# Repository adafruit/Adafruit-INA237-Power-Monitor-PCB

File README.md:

## Adafruit INA237 85V 10A 16-bit DC Current Voltage Power Monitor - STEMMA QT PCB

<a href="http://www.adafruit.com/products/6340"><br/>
Click here to purchase one from the Adafruit shop</a>

PCB files for the Adafruit INA237 85V 10A 16-bit DC Current Voltage Power Monitor - STEMMA QT. 

Format is EagleCAD schematic and board layout
* https://www.adafruit.com/product/6340

### Description

The INA237 is an amazing power monitoring chip, with best-of-everything support: up to 85VDC common-mode, high or low side measurements, 16-bit ADC for precision measurements from milliamp to Amp, and I2C interface for easy configuration of alerts, oversampling, gain adjustments and more!

The INA237 is similar to the INA228, with the same:

* up to +85V high or low-side measurements
* up to 10A or 2.75A
* current, voltage and power measurements

However, unlike the INA228 the INA237:

* has only 16-bit resolution, so 0.15mA or 42uA LSB rather than 10uA/2.5uA
* the INA228 can measure energy/charge for you but the INA237 cannot
* 0.3% gain error, ±50 µV max offset voltage compared to INA228's 0.05% gain error, ±1 µV

This breakout board may well be the last current sensing solution you every need to buy. Not only can it do the work of two multimeters, but it can do it with amazing precision and flexibility. With it you can measure high or low side DC current, the bus voltage, and have it automatically calculate the power. It can do so over impressive voltage, current, and temperature ranges with better than 1% accuracy, all while delivering the data in an easy to use format over I2C.

Works great with any microcontroller that is CircuitPython or Arduino compatible as well as single board computers such as the Raspberry Pi. It is compatible with 3V or 5V logic and can measure bus voltages up to +85VDC. Not for use with AC voltages.

Most current-measuring devices operate with some notable constraints that limit what they can be used for. Many are low-side only which can cause issues as the ground reference changes with current. Others like its little sister the INA219B avoid this by measuring on the high side but need to change their shunt resistor to measure different current ranges. The INA237 avoids these limitations, and with the precision 15milliohm shunt resistor on board, it can be used to measure as much as +85V at up to 10A (~0.15mA per LSB) or 2.75A (~42uA per LSB) Continuous on either the high or low side. Wow!

The voltage across the integrated 15 milliohm (.015 ohms!), 0.1% shunt resistor is measured by the internal 16 bit ADC, allowing for measurements over the current range with a resolution of 0.15mA per LSB in high current measurement mode or 42uA per LSB in low current measurement mode.To measure low-side, Connect VIN- to ground and VIN+ to your load's lowest potential. Cut the jumper on the back that connects VBUS to VIN+: VBUS should connect to the highest project voltage, up to 85V. To measure high-side, connect VIN+ to the highest project voltage, and VIN- to the load's highest potential. In high-side measurement, which is most common, we simplify wiring by having a pre-connected jumper from V+ to VBUS.

Usage is simple. Power the sensor itself with 3 to 5VDC and connect the two I2C pins to your microcontroller. Then connect your target power supply to VIN+ and the load to ground to VIN-. We have a detailed tutorial that will do all the gain, range, and math for you - just plug and go with our Arduino library or CircuitPython! You can connect up to 4 sensors on one bus by soldering the address jumpers on the back.

As if that weren't enough, we also added SparkFun qwiic-compatible STEMMA QT connectors for the I2C bus, so you don't even need to solder the I2C and power lines. Simply wire up to your favorite micro using a STEMMA QT adapter cable. The Stemma QT connectors also mean the INA237 can be used with our various associated accessories. QT Cable is not included, but we have a variety in the shop.

Comes as a fully assembled breakout board with a 3.5mm terminal block and header. Some light soldering is required to attach the header for use in a breadboard. 

### License

Adafruit invests time and resources providing this open source design, please support Adafruit and open-source hardware by purchasing products from [Adafruit](https://www.adafruit.com)!

Designed by Limor Fried/Ladyada for Adafruit Industries.

Creative Commons Attribution/Share-Alike, all text above must be included in any redistribution. 
See license.txt for additional details.

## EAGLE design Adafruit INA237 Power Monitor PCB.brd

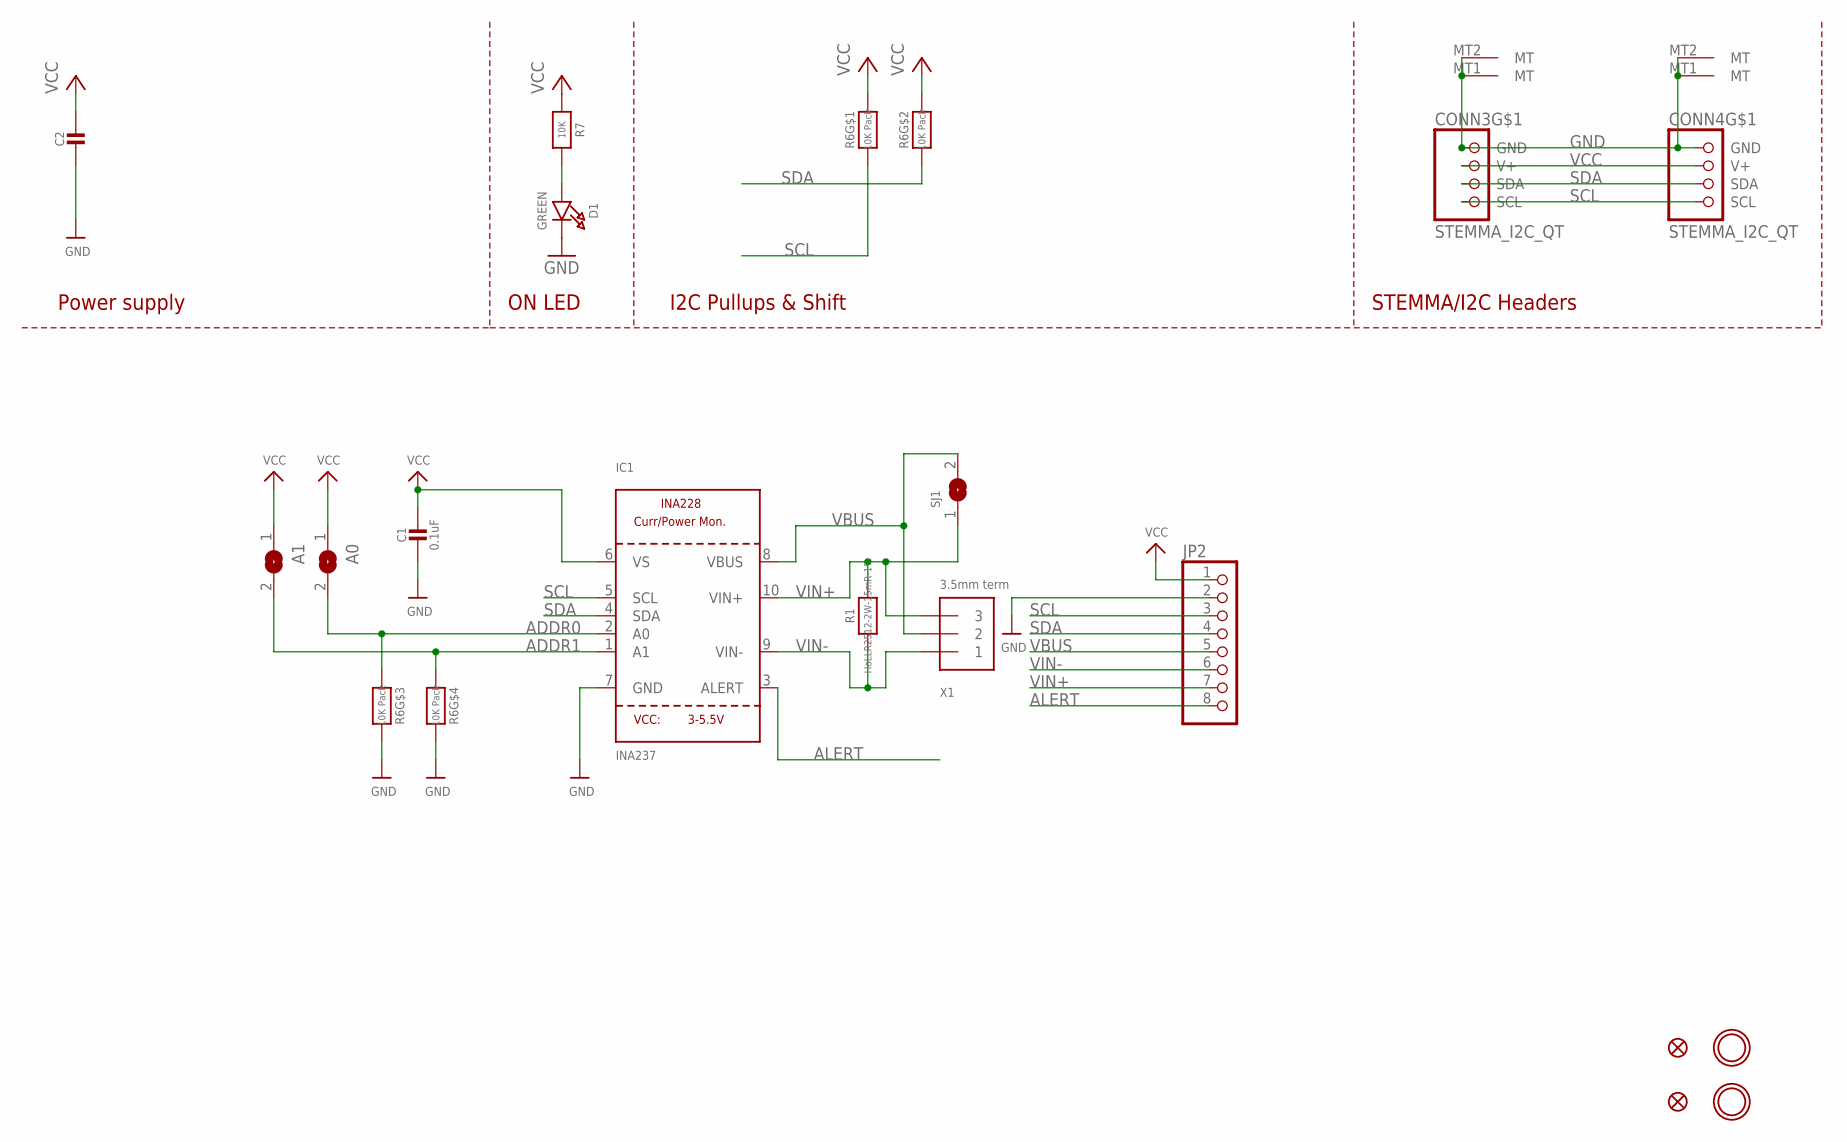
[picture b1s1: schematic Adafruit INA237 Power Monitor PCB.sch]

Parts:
A0, A1: SOLDERJUMPERREFLOW_NOPASTE; SOLDERJUMPER_REFLOW_NOPASTE
C1: 0.1uF; 0603-NO
C2: 10uF; 0805-NO
CONN3, CONN4: STEMMA_I2C_QT; JST_SH4
D1: GREEN; CHIPLED_0603_NOOUTLINE
FID3, FID4: FIDUCIAL_1MM
IC1: INA237; MSOP10
JP2: HEADER-1X870MIL; 1X08_ROUND_70
R1: HoLLR2512-2W-15mR-1%; 2512
R6: 10K Pack; RESPACK_4X0603
R7: 10K; 0603-NO
SJ1: SOLDERJUMPERCLOSED; SOLDERJUMPER_CLOSEDWIRE
U$20, U$21: MOUNTINGHOLE2.5; MOUNTINGHOLE_2.5_PLATED
X1: 3.5mm term; TERMBLOCK_1X3-3.5MM

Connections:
ADDR0: A0.2, IC1.2 (A0), R6.3 (1)
ADDR1: A1.2, IC1.1 (A1), R6.4 (1)
ALERT: IC1.3 (ALERT), JP2.8
GND: C1.2, C2.2, CONN3.1 (GND), CONN3.MT1 (MT), CONN3.MT2 (MT), CONN4.1 (GND), CONN4.MT1 (MT), CONN4.MT2 (MT), D1.C, IC1.7 (GND), JP2.2, R6.5 (2), R6.6 (2)
unnamed: D1.A, R7.2
SCL: CONN3.4 (SCL), CONN4.4 (SCL), IC1.5 (SCL), JP2.3, R6.1
SDA: CONN3.3 (SDA), CONN4.3 (SDA), IC1.4 (SDA), JP2.4, R6.2 (1)
VBUS: IC1.8 (VBUS), JP2.5, SJ1.2, X1.2
VCC: A0.1, A1.1, C1.1, C2.1, CONN3.2 (V+), CONN4.2 (V+), IC1.6 (VS), JP2.1, R6.7 (2), R6.8 (2), R7.1
VIN+: IC1.10 (VIN+), JP2.7, R1.2, SJ1.1, X1.3
VIN-: IC1.9 (VIN-), JP2.6, R1.1, X1.1

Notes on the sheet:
I2C Pullups & Shift
STEMMA/I2C Headers
ON LED
Power supply

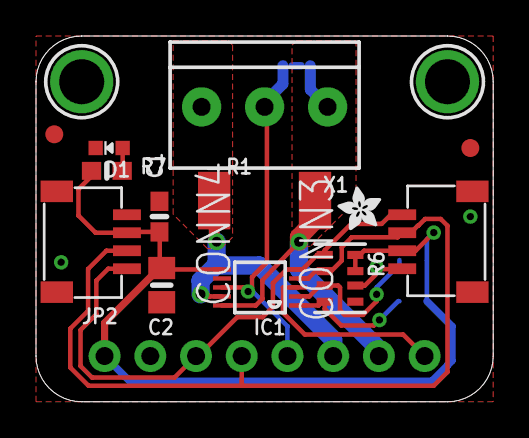
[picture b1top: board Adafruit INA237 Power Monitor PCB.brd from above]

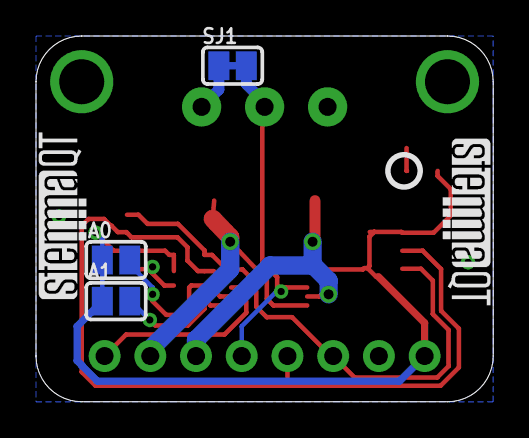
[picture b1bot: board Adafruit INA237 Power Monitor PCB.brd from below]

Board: 2 copper layers, 25.4 x 20.3 mm, 45 parts (17 on the bottom side), 11 nets.

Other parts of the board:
PLABEL0: PLABEL0
PLABEL1: PLABEL1
PLABEL2: PLABEL2
PLABEL3: PLABEL3
PLABEL4: PLABEL4
PLABEL5: PLABEL5
PLABEL6: PLABEL6
PLABEL7: PLABEL7
PLABEL8: PLABEL8
PLABEL9: PLABEL9
PLABEL10: PLABEL10
PLABEL12: PLABEL12
PLABEL13: PLABEL13
PLABEL14: PLABEL14
PLABEL15: PLABEL15
PLABEL16: PLABEL16
PLABEL18: PLABEL18
PLABEL19: PLABEL19
PLABEL20: PLABEL20
PLABEL21: PLABEL21
PLABEL22: PLABEL22
PLABEL23: PLABEL23
PLABEL24: PLABEL24
U$1: ADAFRUIT_2.5MM
U$30: PCBFEAT-REV-040
U$31, U$32: STEMMAQT

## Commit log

2025-06-02 cookiecutter
